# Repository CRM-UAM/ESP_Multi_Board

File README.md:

# ESP_Multi_Board (En constucción)
Diseño de una nueva placa basada en el módulo ESP8266 con conextividad WIFI y extensión para soportar dos motores DC, 8 GPIO digitales (MCP23008), 12 entradas Análogicas (MAX11605EEE+), giroscopio y acelerómetro (MPU6050)

_ESP Multi Boards_

_SMD boards can be soldered using an iron and low-temp solder paste (a.k.a. "¡soldadas con [el método de la plancha!](https://www.youtube.com/watch?v=2VqYg4uM7OA)")_

##Librerias
+ [Arduino IDE for ESP8266](http://www.arduinesp.com/ "ArduinESP")
+ [MCP23008 lib for Arduino](https://github.com/adafruit/Adafruit-MCP23008-library "MCP23008 library")

IR values
cm - val
0 - 216
2 - 130
3 - 92
4 - 73
5 - 53
6 - 40
7 - 34
10 - 21

_Testing the components before sending the PCB out for manufacture_

Authors
--
**Víctor Uceda & Carlos García**  
Club de Robótica-Mecatrónica, Universidad Autónoma de Madrid (CRM-UAM)  
<http://crm.ii.uam.es>  

License
--
License: **Attribution - Share Alike - Creative Commons (<http://creativecommons.org/licenses/by-sa/4.0/>)**  

Disclaimer  
--
This hardware/software is provided "as is", and you use the hardware/software at your own risk. Under no circumstances shall any author be liable for direct, indirect, special, incidental, or consequential damages resulting from the use, misuse, or inability to use this hardware/software, even if the authors have been advised of the possibility of such damages.

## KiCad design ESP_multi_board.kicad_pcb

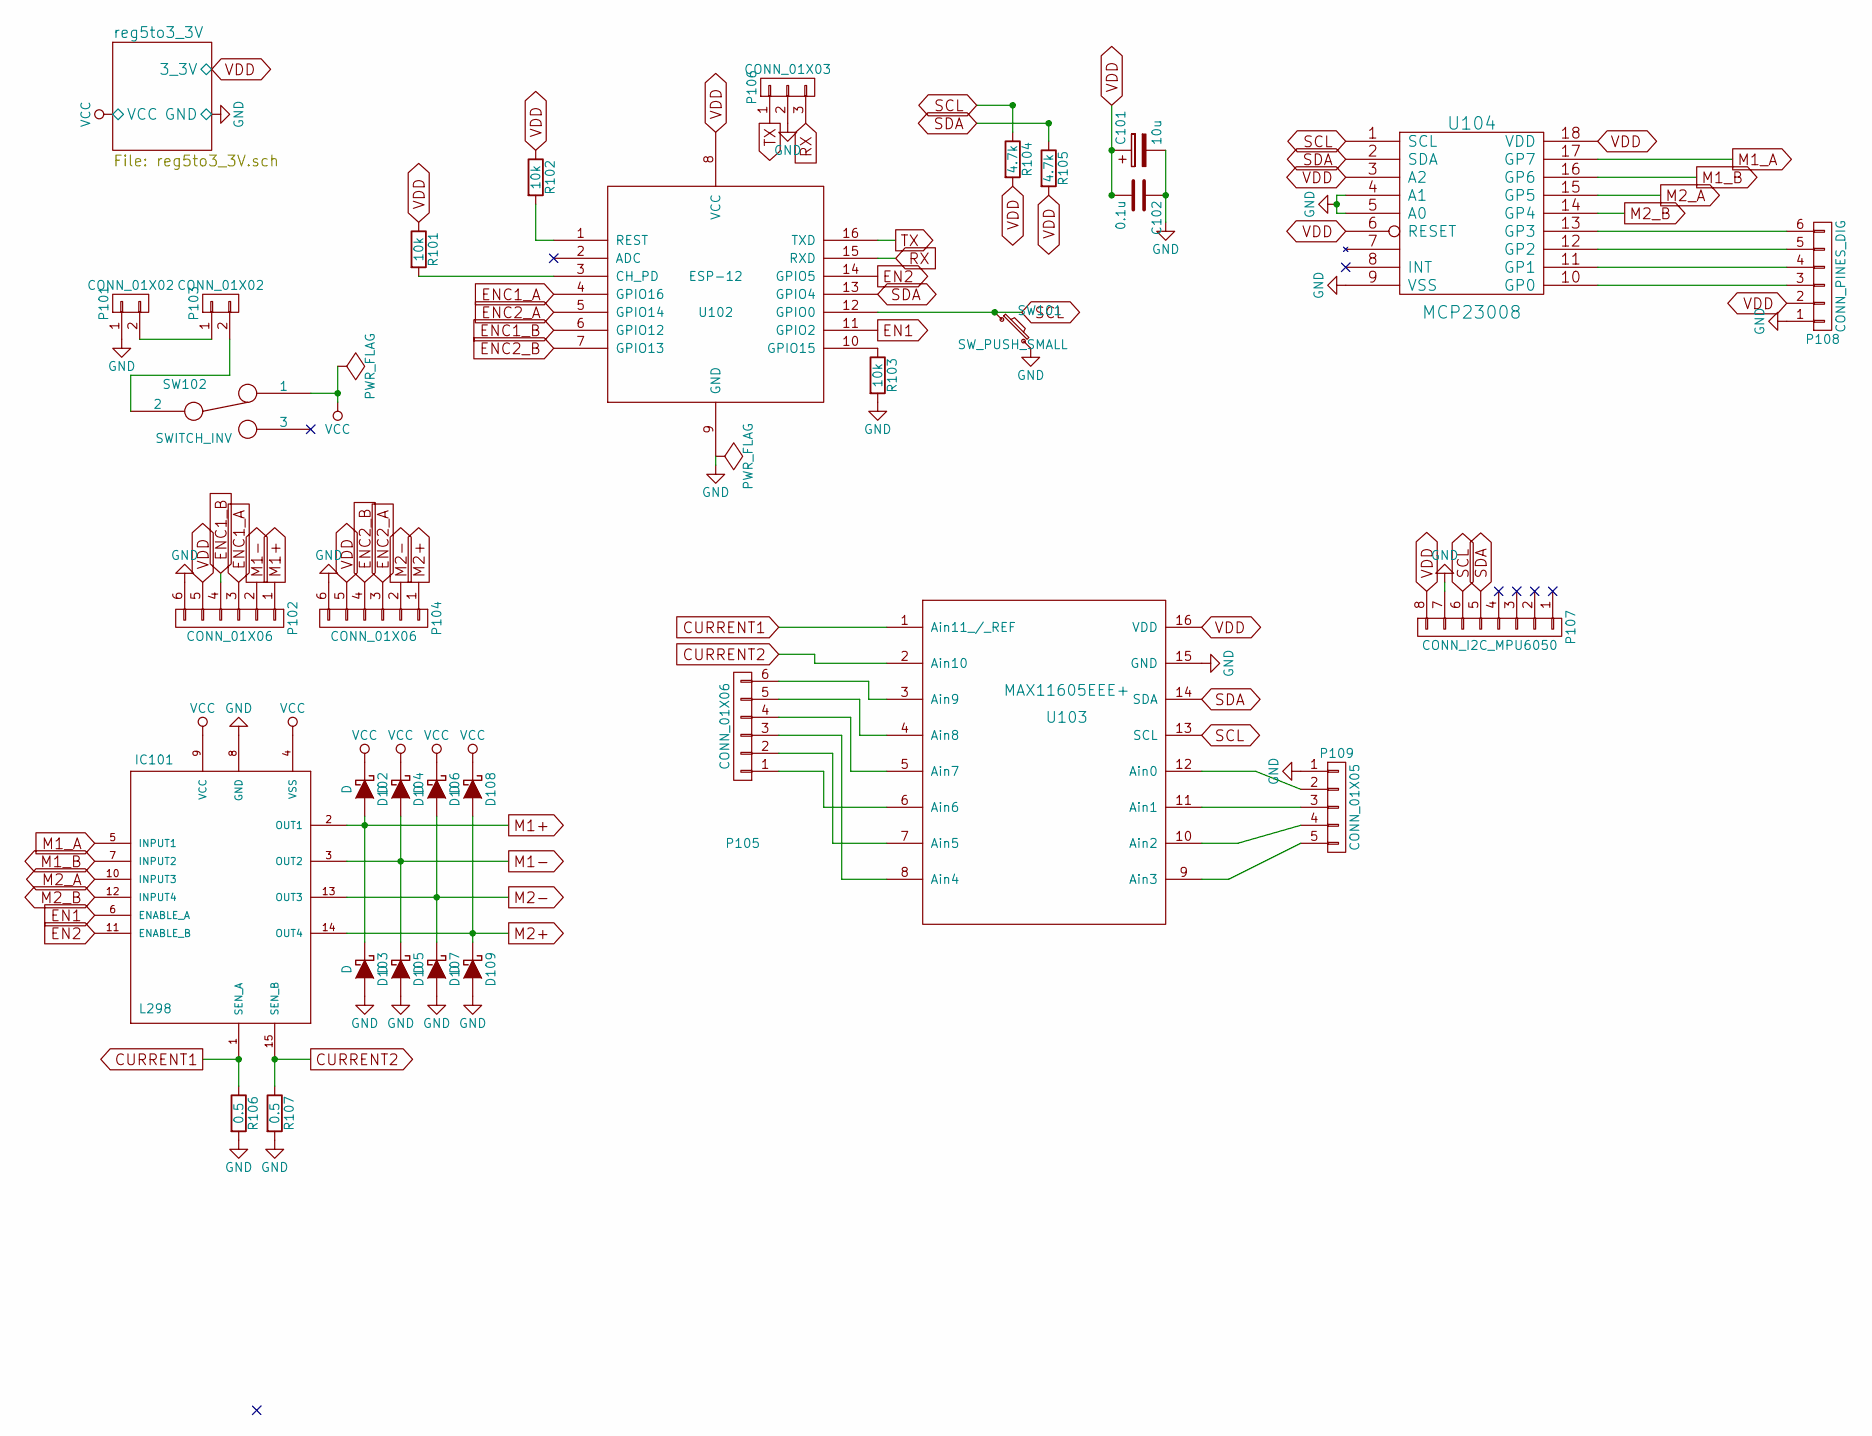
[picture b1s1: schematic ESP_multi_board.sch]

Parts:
C101: 10u; C_1206
C102: 0.1u; C_0805_HandSoldering
D102, D103, D104, D105, D106, D107, D108, D109: D; SMD_D_SMA-Sub-2
IC101: L298; Multiwatt_15_Vertical
P101, P103: CONN_01X02; Pin_Header_Angled_1x02
P102, P104, P105: CONN_01X06; Pin_Header_Straight_1x06
P106: CONN_01X03; Pin_Header_Straight_1x03
P107: CONN_I2C_MPU6050; Socket_Strip_Straight_1x08
P108: CONN_PINES_DIG; Pin_Header_Straight_1x06
P109: CONN_01X05; Pin_Header_Straight_1x05
R101, R102, R103: 10k; R_0805_HandSoldering
R104, R105: 4.7k; R_0805_HandSoldering
R106, R107: 0.5; R_1206
SW101: SW_PUSH_SMALL; SW_SPST_EVPBF
SW102: SWITCH_INV; switch_power_custom
U102: ESP-12
U103: MAX11605EEE+; SSOP-16_3.9x4.9mm_Pitch0.635mm
U104: MCP23008; SOIC-18_7.5x11.6mm_Pitch1.27mm

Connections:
CURRENT1: IC101.1 (SEN_A), R106.1, U103.1 (Ain11_/_REF)
CURRENT2: IC101.15 (SEN_B), R107.1, U103.2 (Ain10)
EN1: IC101.6 (ENABLE_A), U102.11 (GPIO2)
EN2: IC101.11 (ENABLE_B), U102.14 (GPIO5)
ENC1_A: P102.3, U102.4 (GPIO16)
ENC1_B: P102.4, U102.6 (GPIO12)
ENC2_A: P104.3, U102.5 (GPIO14)
ENC2_B: P104.4, U102.7 (GPIO13)
GND: C101.2, C102.1, D103.2 (A), D105.2 (A), D107.2 (A), D109.2 (A), IC101.8 (GND), P101.1, P102.6, P104.6, P106.2, P107.7, P108.1, P109.1, R103.2, R106.2, R107.2, SW101.2, U102.9 (GND), U103.15 (GND), U104.4 (A1), U104.5 (A0), U104.9 (VSS); also elsewhere on the board
M1+: D102.2 (A), D103.1 (K), IC101.2 (OUT1), P102.1
M1-: D104.2 (A), D105.1 (K), IC101.3 (OUT2), P102.2
M1_A: IC101.5 (INPUT1), U104.17 (GP7)
M1_B: IC101.7 (INPUT2), U104.16 (GP6)
M2+: D108.2 (A), D109.1 (K), IC101.14 (OUT4), P104.1
M2-: D106.2 (A), D107.1 (K), IC101.13 (OUT3), P104.2
M2_A: IC101.10 (INPUT3), U104.15 (GP5)
M2_B: IC101.12 (INPUT4), U104.14 (GP4)
unnamed: P101.2, P103.1
unnamed: P103.2, SW102.2
unnamed: P105.1, U103.6 (Ain6)
unnamed: P105.2, U103.7 (Ain5)
unnamed: P105.3, U103.8 (Ain4)
unnamed: P105.4, U103.5 (Ain7)
unnamed: P105.5, U103.4 (Ain8)
unnamed: P105.6, U103.3 (Ain9)
unnamed: P108.3, U104.10 (GP0)
unnamed: P108.4, U104.11 (GP1)
unnamed: P108.5, U104.12 (GP2)
unnamed: P108.6, U104.13 (GP3)
unnamed: P109.2, U103.12 (Ain0)
unnamed: P109.3, U103.11 (Ain1)
unnamed: P109.4, U103.10 (Ain2)
unnamed: P109.5, U103.9 (Ain3)
unnamed: R101.2, U102.3 (CH_PD)
unnamed: R102.2, U102.1 (REST)
unnamed: R103.1, U102.10 (GPIO15)
RX: P106.3, U102.15 (RXD)
SCL: P107.6, R104.1, SW101.1, U102.12 (GPIO0), U103.13 (SCL), U104.1 (SCL)
SDA: P107.5, R105.1, U102.13 (GPIO4), U103.14 (SDA), U104.2 (SDA)
TX: P106.1, U102.16 (TXD)
VCC: D102.1 (K), D104.1 (K), D106.1 (K), D108.1 (K), IC101.4 (VSS), IC101.9 (VCC), SW102.1; also elsewhere on the board
VDD: C101.1, C102.2, P102.5, P104.5, P107.8, P108.2, R101.1, R102.1, R104.2, R105.2, U102.8 (VCC), U103.16 (VDD), U104.3 (A2), U104.6 (RESET), U104.18 (VDD); also elsewhere on the board

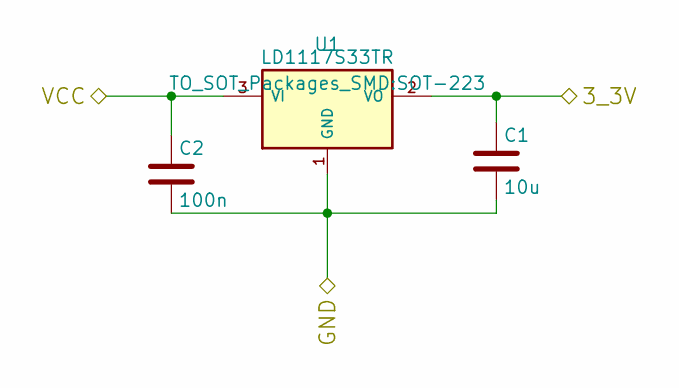
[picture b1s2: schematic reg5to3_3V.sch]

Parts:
C1: 10u; C_1206
C2: 100n; C_0805_HandSoldering
U1: LD1117S33TR; SOT-223

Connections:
GND: C1.2, C2.2, U1.1 (GND); also elsewhere on the board
VCC: C2.1, U1.3 (VI); also elsewhere on the board
VDD: C1.1, U1.2 (VO); also elsewhere on the board

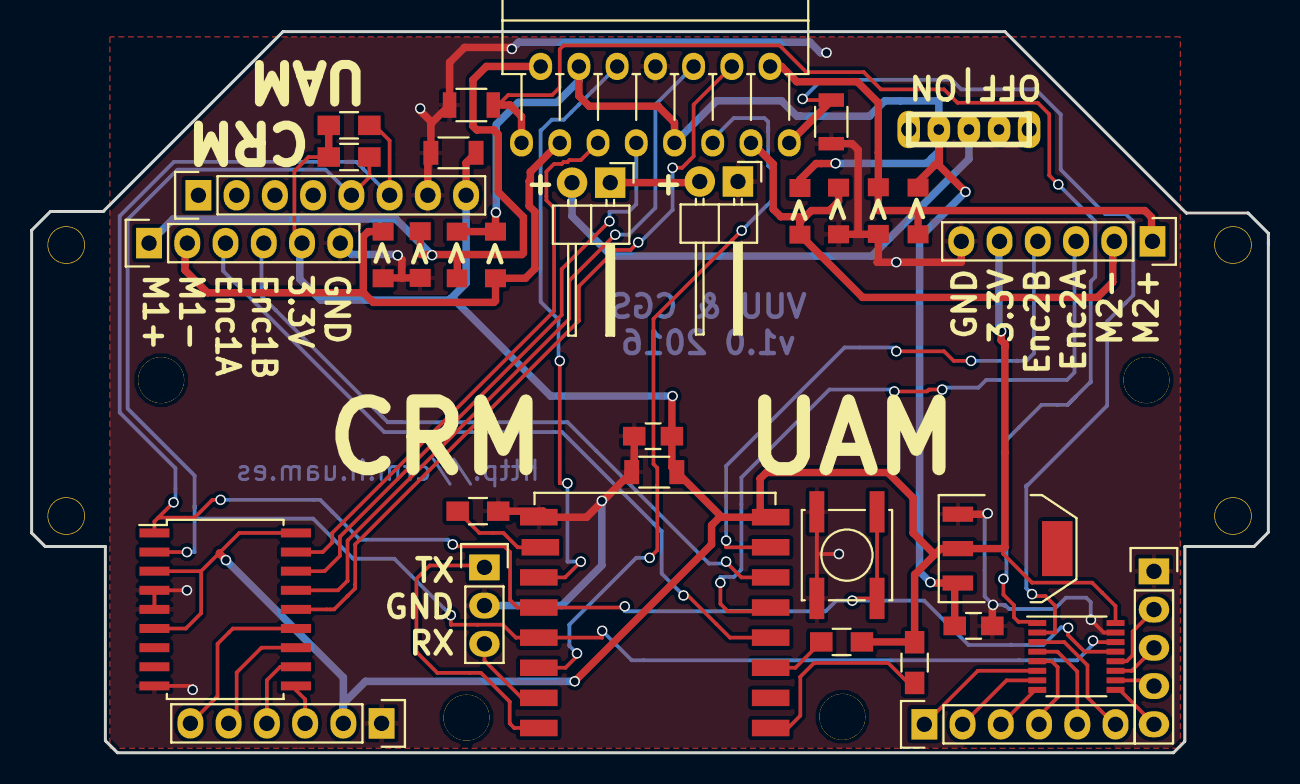
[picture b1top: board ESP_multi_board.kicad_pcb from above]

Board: 2 copper layers, 82.1 x 47.9 mm, 45 parts (0 on the bottom side), 42 nets.

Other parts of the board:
drill3, drill4, drill7, drill8, drill8#2, drill8#3, drill9, drill11, drill14, drill20: 1pin

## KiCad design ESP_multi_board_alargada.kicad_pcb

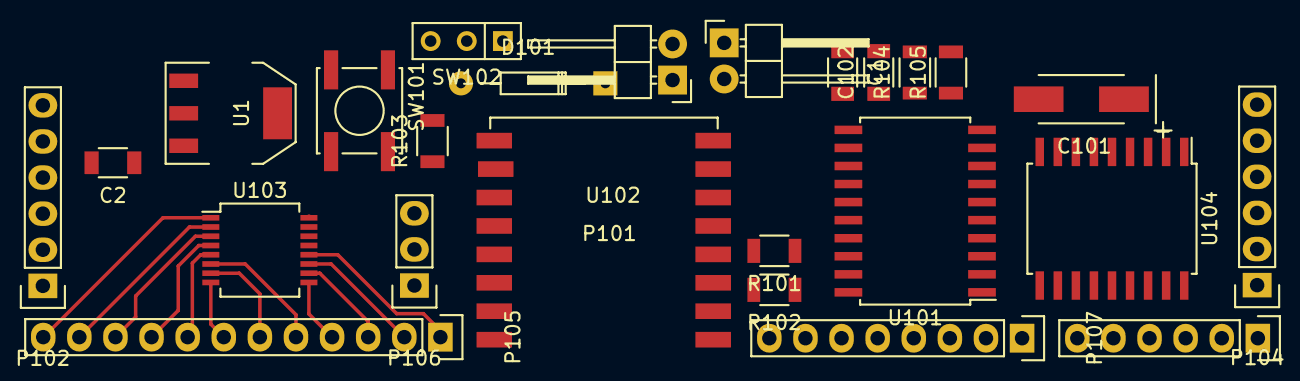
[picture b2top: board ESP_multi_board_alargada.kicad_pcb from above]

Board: 2 copper layers, 25 parts (0 on the bottom side), 43 nets.

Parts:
C1: 10u; C_1206
C2: 100n; C_1206
C101: 10u; TantalC_SizeC_EIA-6032_HandSoldering
C102: 0.1u; C_1206
D101: D; Diode_DO-35_SOD27_Horizontal_RM10
P101, P103: CONN_01X02; Pin_Header_Angled_1x02
P102, P104: CONN_01X06; Pin_Header_Straight_1x06
P105: CONN_01X12; Pin_Header_Straight_1x12
P106: CONN_01X03; Pin_Header_Straight_1x03
P107: CONN_I2C_MPU6050; Pin_Header_Straight_1x08
P108: CONN_PINES_DIG; Pin_Header_Straight_1x06
R101, R102, R103: 10k; R_1206
R104, R105: 47k; R_1206
SW101: SW_PUSH_SMALL; SW_SPST_EVPBF
SW102: SWITCH_INV; SW_Micro_SPST
U1: LD1117S33TR; SOT-223
U101: L293DD; SOIC-20_7.5x12.8mm_Pitch1.27mm
U102: ESP-12
U103: MAX11605EEE+; SSOP-16_5.3x6.2mm_Pitch0.65mm
U104: MCP23008; SOIC-18_7.5x11.6mm_Pitch1.27mm

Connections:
EN1: U101.1, U102.11
EN2: U101.11, U102.14
ENC1_A: P102.5, U102.4
ENC1_B: P102.6, U102.6
ENC2_A: P104.5, U102.5
ENC2_B: P104.6, U102.7
GND: C1.2, C2.2, C101.2, C102.1, P101.1, P102.4, P104.4, P106.2, P107.2, P107.7, P108.1, R103.2, SW101.2, U1.1, U101.4, U101.5, U101.6, U101.7, U101.14, U101.15, U101.16, U101.17, U102.9, U103.15, U104.4, U104.5, U104.9
M1+: P102.1, U101.3
M1-: P102.2, U101.8
M1_A: U101.2, U104.10
M1_B: U101.9, U104.11
M2+: P104.1, U101.18
M2-: P104.2, U101.13
M2_A: U101.19, U104.12
M2_B: U101.12, U104.13
unnamed: D101.1, P101.2
unnamed: D101.2, SW102.2
unnamed: P103.1, SW102.1
unnamed: P105.1, U103.12
unnamed: P105.2, U103.11
unnamed: P105.3, U103.10
unnamed: P105.4, U103.9
unnamed: P105.5, U103.6
unnamed: P105.6, U103.7
unnamed: P105.7, U103.8
unnamed: P105.8, U103.5
unnamed: P105.9, U103.4
unnamed: P105.10, U103.3
unnamed: P105.11, U103.2
unnamed: P105.12, U103.1
unnamed: P108.3, U104.17
unnamed: P108.4, U104.16
unnamed: P108.5, U104.15
unnamed: P108.6, U104.14
unnamed: R101.2, U102.3
unnamed: R102.2, U102.1
unnamed: R103.1, U102.10
RX: P106.3, U102.15
SCL: P107.6, R104.1, SW101.1, U102.12, U103.13, U104.1
SDA: P107.5, R105.1, U102.13, U103.14, U104.2
TX: P106.1, U102.16
VCC: C2.1, P103.2, U1.3, U101.10
VDD: C1.1, C101.1, C102.2, P102.3, P104.3, P107.8, P108.2, R101.1, R102.1, R104.2, R105.2, U1.2, U101.20, U102.8, U103.16, U104.3, U104.6, U104.18

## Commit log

2016-04-13 initial commit. schematic
2016-04-13 gitignore
2016-04-13 added some necesary libs
2016-04-16 Reg5Vto3.3V añadido como hoja jerarquica, añadido conector I2C externo, añadido resistencia ESP
2016-04-17 incluido conectores I2C externos para el MPU6050\n modificado JUMPER1
2016-04-17 modificado jumper1
2016-04-17 resueltos probelams con duplicados y checkeado esquematico
2016-04-17 intento de asginar huellas
2016-04-17 nuevo componente diseñado L293DD, asignadas huellas
2016-04-17 intento de hacer path
2016-04-17 pendiente de enrutar, TODO: incluir diodos baterias, meditar los jumpers
2016-04-18 actualizaciones en CRM. TODO: cambiar L293DD por L298smd, cambiar para controlar ENs con pwm, y pines de direccion de motores desde el extensor de pines, eliminar jumpers, ajustar tamaño de las resis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
2016-04-18 incluido DAC 4canales MCP4728, modificados conexion de motores para hacer pwm en los enables
2016-04-18 modificada huella del jumper, incluidos condensadores en la linea de 3.3v
2016-04-19 autorouting generado con freerouting
2016-04-19 cambio de posiciones en la placa
2016-04-27 versión quasifinal
2016-04-27 vesion simplificada, sin jumper y sinconectar los pines de int
2016-04-27 cambio de posición ADC y L293DD
2016-04-28 incluida version de la placa alargada 10x2.5 cm
2016-04-28 cambios para hacer la version alargada mas compacta
2016-04-29 routing
2016-04-30 cambio a L298 con diodos
2016-04-30 asignadas huellas diodos, provisionales
2016-04-30 huellas diodos actualizadas
2016-05-01 organizacion directorio
2016-05-01 limpieza repo
2016-05-01 Readme
2016-05-01 limpieza
2016-05-01 nueva placa con hueco para motores integrado
2016-05-02 motores mas juntos en la PCB
2016-05-03 Actualizadas huellas de acuerdo a los componentes de Mouser
2016-05-12 placa actualizada
2016-05-13 placa final con doble agujeros (sin doble troquel)
2016-05-17 limpiada (dobles elementos) y con refeencias unicas
2016-05-18 Cambios en el layout y rutado de las pistas de corriente
2016-05-18 Finalizado posible layout
2016-05-18 Añadido texto al silkscreen (autores, año y versión), y generados los ficheros Gerber
2016-07-06 Labeled components with their values
2016-08-30 Libreria para controlar el chip MCP modificada para usar los pines SDA y SCL apropiados al ESP-12
2016-08-30 Codigos de ejemplos simples para probar la entrada y salida digital (MCP) y los motores (L293)
2016-08-31 Codigo de ejemplo de lectura de los pines analogicos, comunicacion con el chip MAX11605EEE+
2016-08-31 library to control ESP_Multi_Board v1.0
2016-09-01 añadida funcionalidad de los encoders
2016-09-01 conflicto analogRead
2016-09-04 dxf files
2016-09-04 lib test and close-loop motors examples
2016-09-04 Added IR sensor support
2016-09-04 Rounded corners design. Added license, picture & readme.
2016-09-06 firmware update and test to use IR sensors
2016-09-06 IR curve values
2016-09-06 Added analog_scand of secuencial analog ports (only 1 I2C read)
2016-09-06 Ejemplo de lectura de los sensores IR, comentado el modo scand para leer los 3 en paralelo
2016-09-13 speed controller module to control robot with a specific speed (using a speed profile with const acc). v0.1-no-compile
2016-09-15 read 3 IR sensor with fast I2C
2016-09-15 speed controller ajusted + telnet telemetry system
2016-09-16 cambios para corregir la curva de actuacion de los motores DC
2016-09-16 lectura multiple IR
2016-09-16 speed controller with one IR error, wall follower
2016-09-18 modificaciones del control de velocidad y control de giro
2016-09-19 ajuste de magnitudes, tiempos y velocidad del giro (calculos en Excel)
2016-10-19 cambios seguir pared 19-oct
2016-11-29 Añadidas fotos
